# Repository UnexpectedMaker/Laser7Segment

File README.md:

# Laser7Segment Display Library
An API that lets you display numbers and letters on Laser7Segment RGB LED displays that are available from [tindie](https://www.tindie.com/products/seonr/laser-segment-display/)

You can find the Open Source hardware PCB design and Gerber files here too as well as the DXF laser cut design files

## Installing and Use
The downloaded code should be added to your arduino IDE libraries folder, and the library requires the [Adafruit NeoPixel library](https://github.com/adafruit/Adafruit_NeoPixel) for it to function.

To include the Laser7Segment library in your project:

    #include <Laser7Segment.h>

You can then initialise the display with the following line that includes the number of Laser7Segment digits and the GPIO to control them:

    Laser7Segment disp( 5, 4 );

You then start the display with the bebin method, passing the brightness:

    disp.Begin(80);

The you simply pass the display the String you would like displayed and a color:

    disp.DisplayText( "1234", disp.Color( 255,0,0) );

Enjoy!

# Support Unexpected Maker

I love designing, making and releasing our projects as open source. I do it because I believe it’s important to share knowledge and give back to the community, like many have done before me. It helps us all learn and grow.

That said, a lot of time, effort and finances have gone into designing and releasing these files, so please consider supporting me by buy some of my TiinyPICO products:

https://tinypico.com/shop

Or by buying one of our products on tindie:

https://www.tindie.com/stores/seonr/

Or by becoming a Patron:

https://www.patreon.com/unexpectedmaker

# Unexpected Maker
http://youtube.com/c/unexpectedmaker

http://twitter.com/unexpectedmaker

https://www.facebook.com/unexpectedmaker/

https://www.instagram.com/unexpectedmaker/

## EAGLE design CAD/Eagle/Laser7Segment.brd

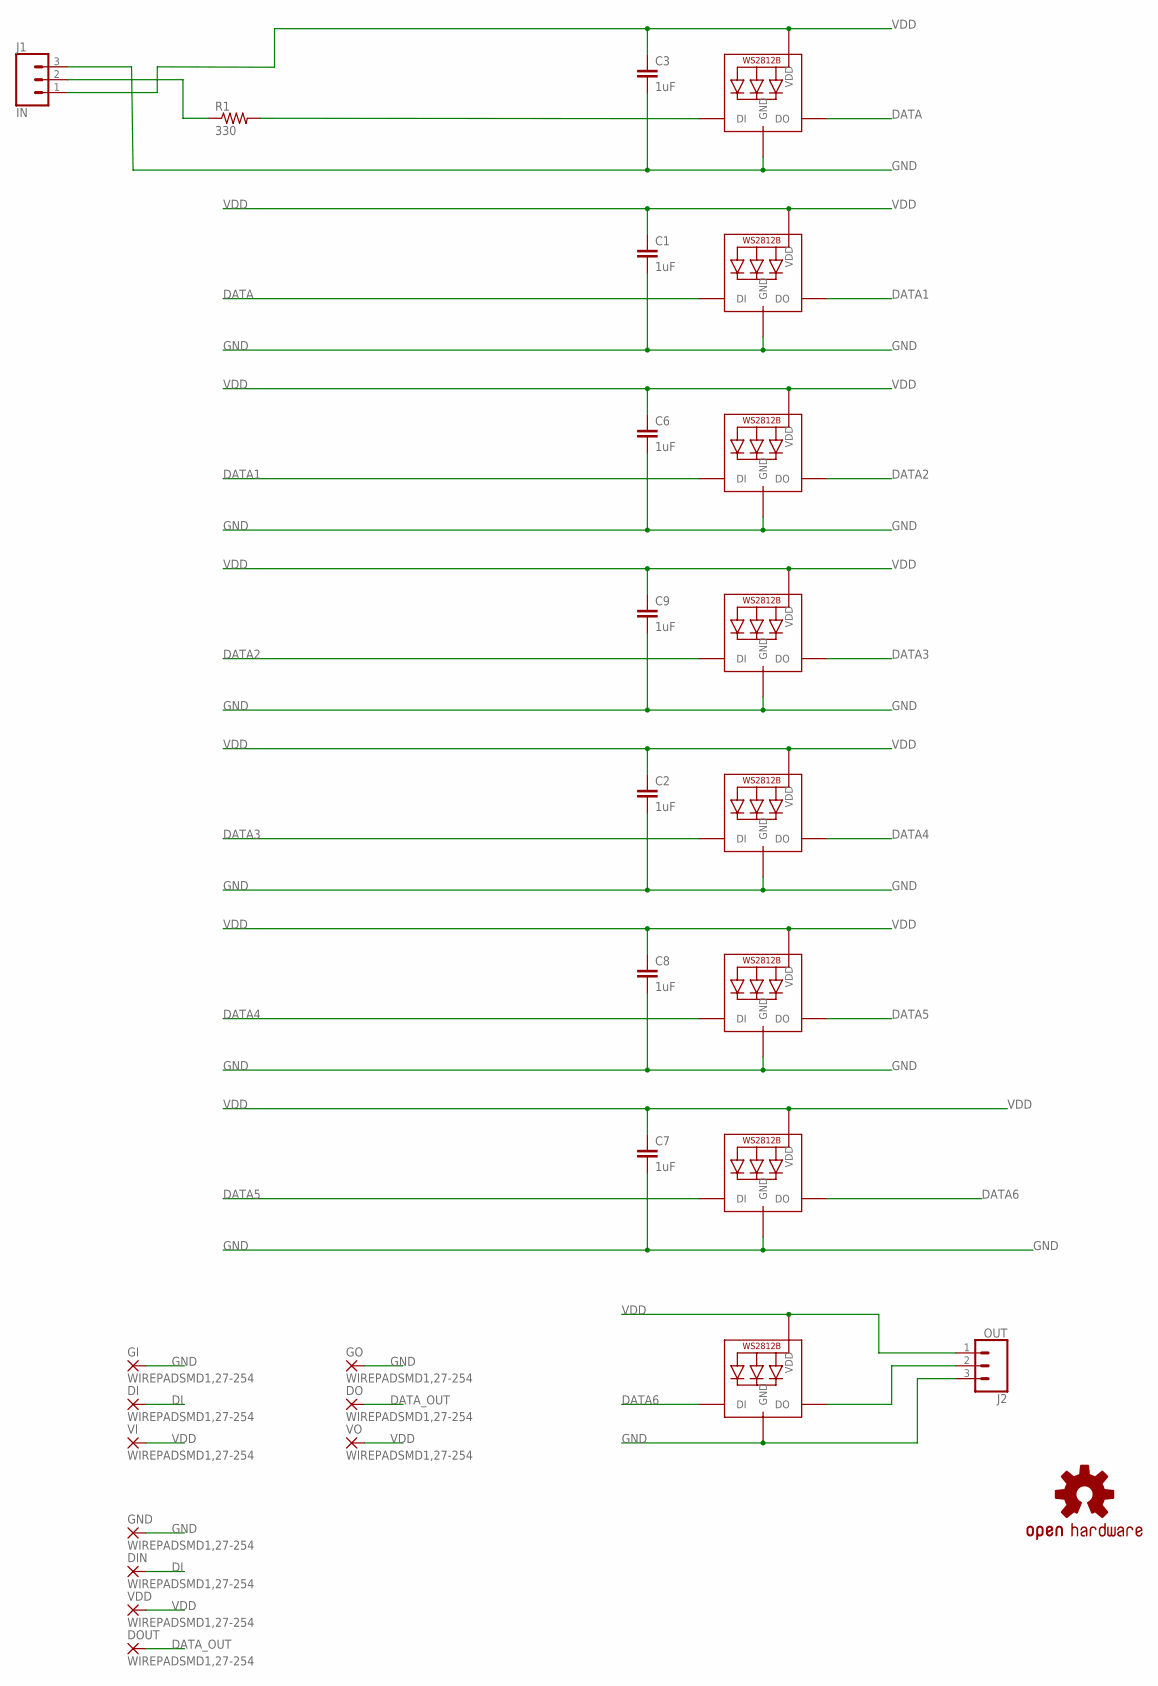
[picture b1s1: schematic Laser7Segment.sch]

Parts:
C1, C2, C3, C6, C7, C8, C9: 1uF; C0805
DI: WIREPADSMD1,27-254; SMD1,27-2,54
DIN: WIREPADSMD1,27-254; SMD1,27-2,54
DO: WIREPADSMD1,27-254; SMD1,27-2,54
DOUT: WIREPADSMD1,27-254; SMD1,27-2,54
GI: WIREPADSMD1,27-254; SMD1,27-2,54
GND: WIREPADSMD1,27-254; SMD1,27-2,54
GO: WIREPADSMD1,27-254; SMD1,27-2,54
J1: IN; 1X03_LONGPADS
J2: OUT; 1X03_LONGPADS
L1, L2, L3, L4, L5, L6, L7: WS2812B5050; WS2812B
L8: RGB 3535; LED3535
LOGO1: OSHW-LOGOM; OSHW-LOGO-M
R1: 330; R0805
VDD: WIREPADSMD1,27-254; SMD1,27-2,54
VI: WIREPADSMD1,27-254; SMD1,27-2,54
VO: WIREPADSMD1,27-254; SMD1,27-2,54

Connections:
DATA: L1.2-DOUT (DO), L2.4-DIN (DI)
DATA1: L2.2-DOUT (DO), L3.4-DIN (DI)
DATA2: L3.2-DOUT (DO), L4.4-DIN (DI)
DATA3: L4.2-DOUT (DO), L5.4-DIN (DI)
DATA4: L5.2-DOUT (DO), L6.4-DIN (DI)
DATA5: L6.2-DOUT (DO), L7.4-DIN (DI)
DATA6: L7.2-DOUT (DO), L8.1 (DI)
DATA_OUT: DO.1, DOUT.1, J2.2, L8.3 (DO)
DI: DI.1, DIN.1, J1.2, R1.1
DI_R: L1.4-DIN (DI), R1.2
GND: C1.2, C2.2, C3.2, C6.2, C7.2, C8.2, C9.2, GI.1, GND.1, GO.1, J1.3, J2.3, L1.3-GND (GND), L2.3-GND (GND), L3.3-GND (GND), L4.3-GND (GND), L5.3-GND (GND), L6.3-GND (GND), L7.3-GND (GND), L8.4 (GND)
VDD: C1.1, C2.1, C3.1, C6.1, C7.1, C8.1, C9.1, J1.1, J2.1, L1.1-VDD (VDD), L2.1-VDD (VDD), L3.1-VDD (VDD), L4.1-VDD (VDD), L5.1-VDD (VDD), L6.1-VDD (VDD), L7.1-VDD (VDD), L8.2 (VDD), VDD.1, VI.1, VO.1

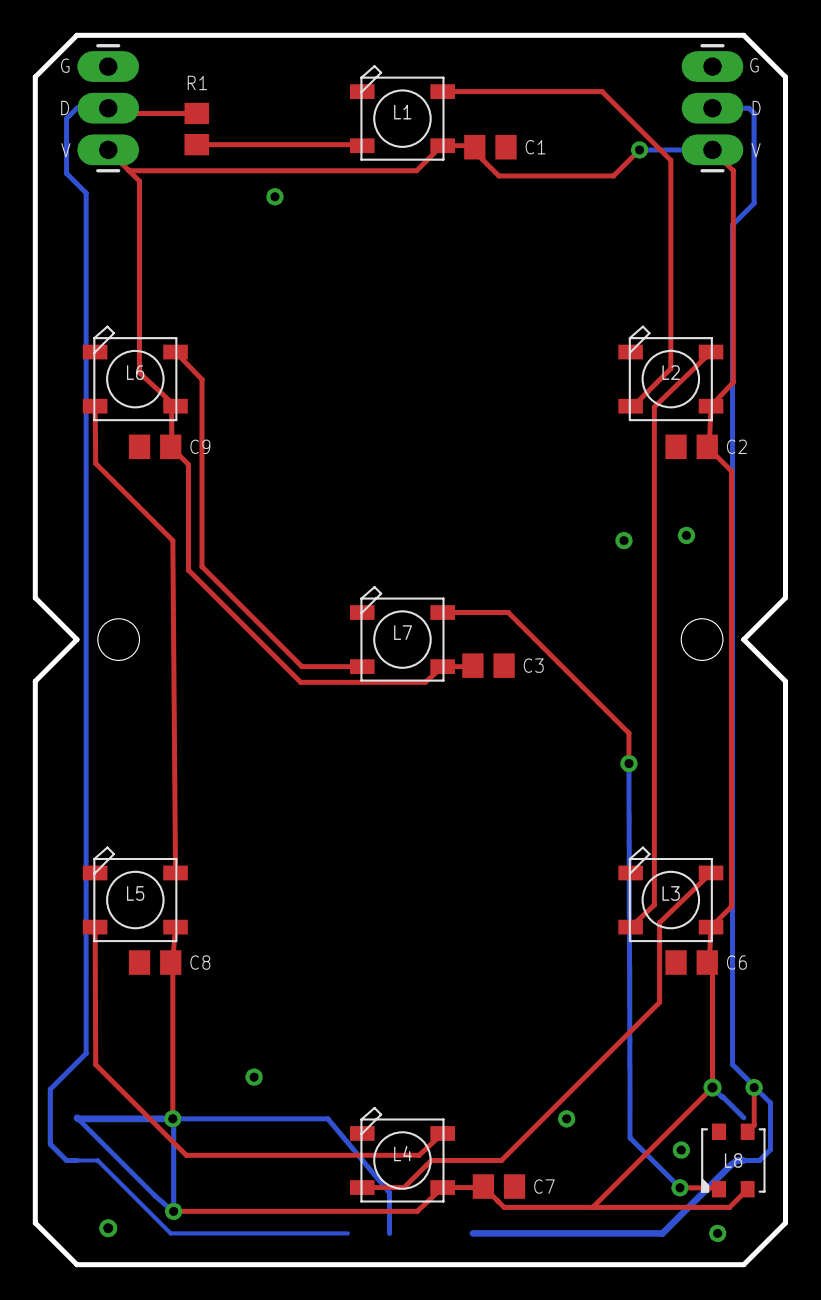
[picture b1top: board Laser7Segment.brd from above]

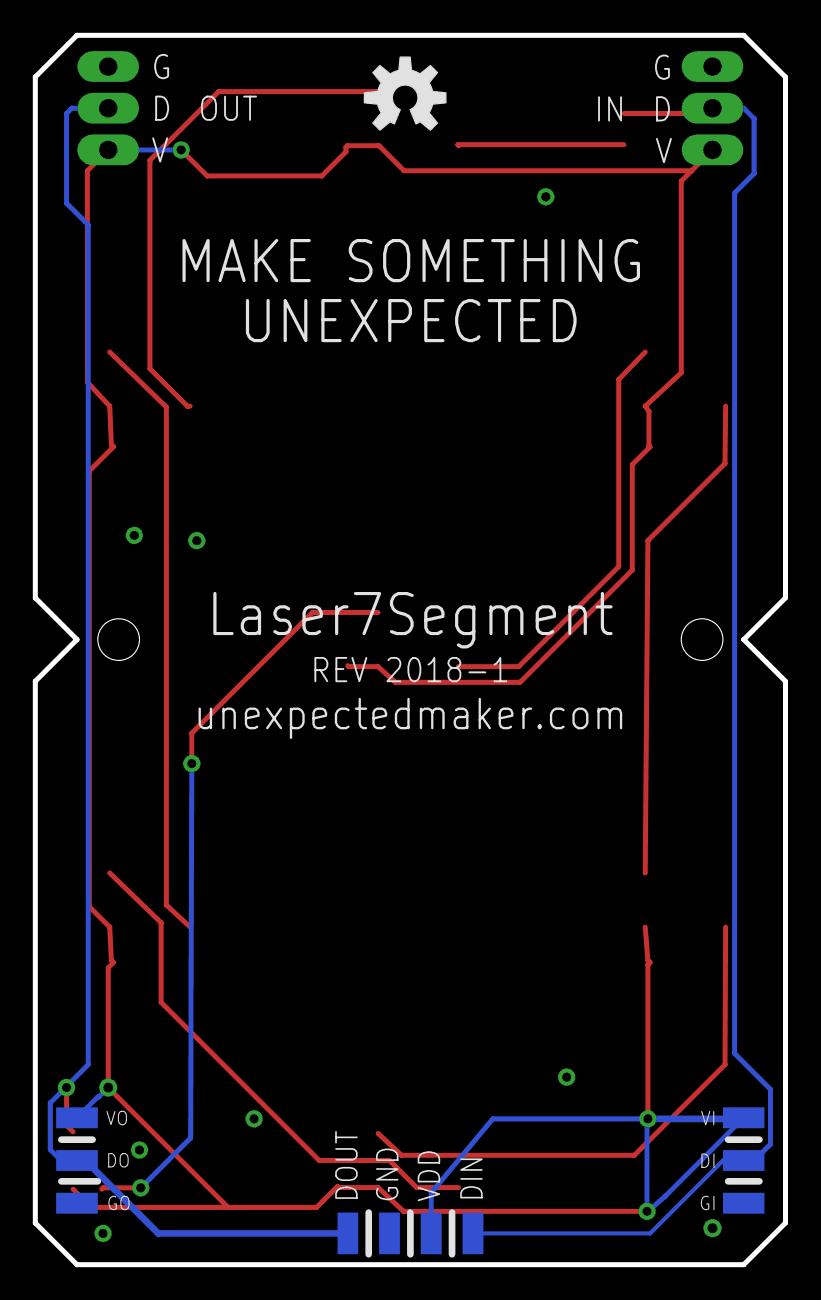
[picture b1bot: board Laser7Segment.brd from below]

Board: 2 copper layers, 45.7 x 74.9 mm, 29 parts (11 on the bottom side), 12 nets.

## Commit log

2018-12-03 Fixed readme

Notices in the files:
parts and their libraries:
SparkFun-Connectors: Licensing: Creative Commons ShareAlike 4.0 International - https://creativecommons.org/licenses/by-sa/4.0
